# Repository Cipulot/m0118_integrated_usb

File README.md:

# m0118_integrated_usb

Drop-in replacement USB-C PCB for the Apple M0118 powered by QMK and VIAL.

## Daughterboard
The board comes with a snappable daughterboard with onboard USB-C. To avoid extra costs no connector is used. Instead the user will solder wires accordingly to the pin correspondence (marked on the PCB).

## Internal Wire
Internal wiring of a USB cable is possible. For this reason 2 holes on the pcb are available to the user. You can use them to tie down the cable using a zip tie for added stability.

An extra pin is provided, the `Shiled` pin. This is electrically connected to the board GND and it's solely used to avoid clipping the shielding wire off from the cable (if present at all).

### hahahahaha funny QR

## Firmware

~~Firmware is in development. Keep an eye out on the commits for it.~~

Firmware is OUT!! Precompiled VIAL `.hex` file downloadable [here](https://github.com/Cipulot/m0118_integrated_usb/blob/main/Firmware/HEX/m0118_integrated_usb_vial.hex).

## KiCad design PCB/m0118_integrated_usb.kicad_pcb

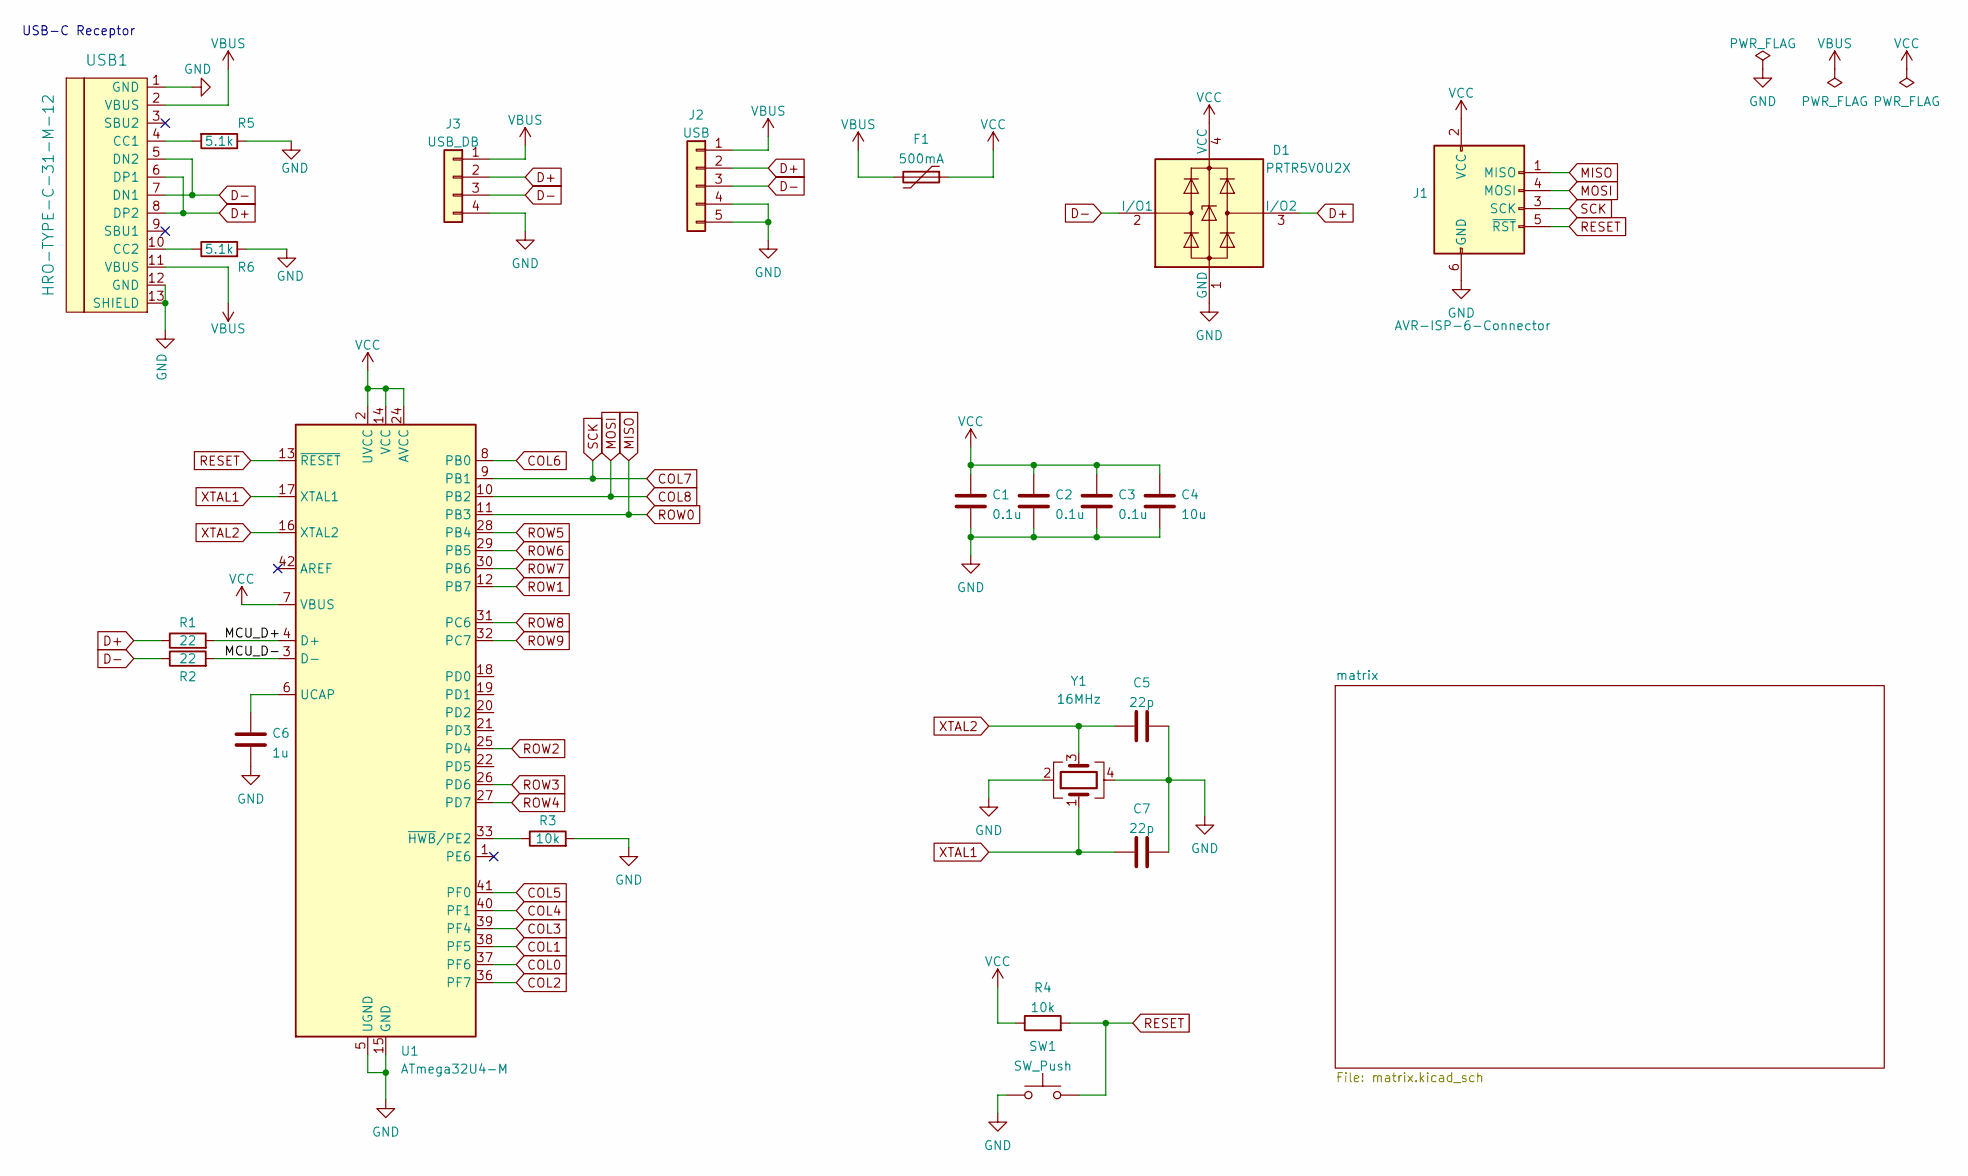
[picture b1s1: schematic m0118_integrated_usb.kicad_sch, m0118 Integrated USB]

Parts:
C1, C2, C3: 0.1u; C_0805_2012Metric
C4: 10u; C_0805_2012Metric
C5, C7: 22p; C_0805_2012Metric
C6: 1u; C_0805_2012Metric
D1: PRTR5V0U2X; SOT-143
F1: 500mA; Fuse_1206_3216Metric
J1: AVR-ISP-6-Connector; Reset_Pretty
J2: USB; PinHeader_1x05_P2.54mm_Vertical
J3: USB_DB; PinHeader_1x04_P2.54mm_Vertical
R1, R2: 22; R_0805_2012Metric
R3, R4: 10k; R_0805_2012Metric
R5, R6: 5.1k; R_0603_1608Metric
SW1: SW_Push; PinHeader_1x02_P2.54mm_Vertical
U1: ATmega32U4-M; QFN-44-1EP_7x7mm_P0.5mm_EP5.2x5.2mm
USB1: HRO-TYPE-C-31-M-12; HRO-TYPE-C-31-M-12-Assembly
Y1: 16MHz; Crystal_SMD_3225-4pin_3.2x2.5mm

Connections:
/MCU_D+: R1.2, U1.4 (D+)
/MCU_D-: R2.2, U1.3 (D-)
COL0: U1.37 (PF6); also elsewhere on the board
COL1: U1.38 (PF5); also elsewhere on the board
COL2: U1.36 (PF7); also elsewhere on the board
COL3: U1.39 (PF4); also elsewhere on the board
COL4: U1.40 (PF1); also elsewhere on the board
COL5: U1.41 (PF0); also elsewhere on the board
COL6: U1.8 (PB0); also elsewhere on the board
COL7: J1.3 (SCK), U1.9 (PB1); also elsewhere on the board
COL8: J1.4 (MOSI), U1.10 (PB2); also elsewhere on the board
D+: D1.3 (I/O2), J2.2, J3.2, R1.1, USB1.6 (DP1), USB1.8 (DP2)
D-: D1.2 (I/O1), J2.3, J3.3, R2.1, USB1.5 (DN2), USB1.7 (DN1)
GND: C1.2, C2.2, C3.2, C4.2, C5.1, C6.2, C7.1, D1.1 (GND), J1.6 (GND), J2.4, J2.5, J3.4, R3.2, R5.1, R6.2, SW1.1, U1.5 (UGND), U1.15 (GND), U1.23 (GND), U1.35 (GND), U1.43 (GND), U1.45 (GND), USB1.1 (GND), USB1.12 (GND), USB1.13 (SHIELD), Y1.2, Y1.4
MISO: J1.1 (MISO), U1.11 (PB3); also elsewhere on the board
unnamed: C6.1, U1.6 (UCAP)
unnamed: R3.1, U1.33 (~HWB/PE2)
unnamed: R5.2, USB1.4 (CC1)
unnamed: R6.1, USB1.10 (CC2)
RESET: J1.5 (~RST), R4.2, SW1.2, U1.13 (~RESET)
ROW1: U1.12 (PB7); also elsewhere on the board
ROW2: U1.25 (PD4); also elsewhere on the board
ROW3: U1.26 (PD6); also elsewhere on the board
ROW4: U1.27 (PD7); also elsewhere on the board
ROW5: U1.28 (PB4); also elsewhere on the board
ROW6: U1.29 (PB5); also elsewhere on the board
ROW7: U1.30 (PB6); also elsewhere on the board
ROW8: U1.31 (PC6); also elsewhere on the board
ROW9: U1.32 (PC7); also elsewhere on the board
VBUS: F1.2, J2.1, J3.1, USB1.2 (VBUS), USB1.11 (VBUS)
VCC: C1.1, C2.1, C3.1, C4.1, D1.4 (VCC), F1.1, J1.2 (VCC), R4.1, U1.2 (UVCC), U1.7 (VBUS), U1.14 (VCC), U1.24 (AVCC), U1.34 (VCC), U1.44 (AVCC)
XTAL1: C7.2, U1.17 (XTAL1), Y1.1
XTAL2: C5.2, U1.16 (XTAL2), Y1.3

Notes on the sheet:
USB-C Receptor

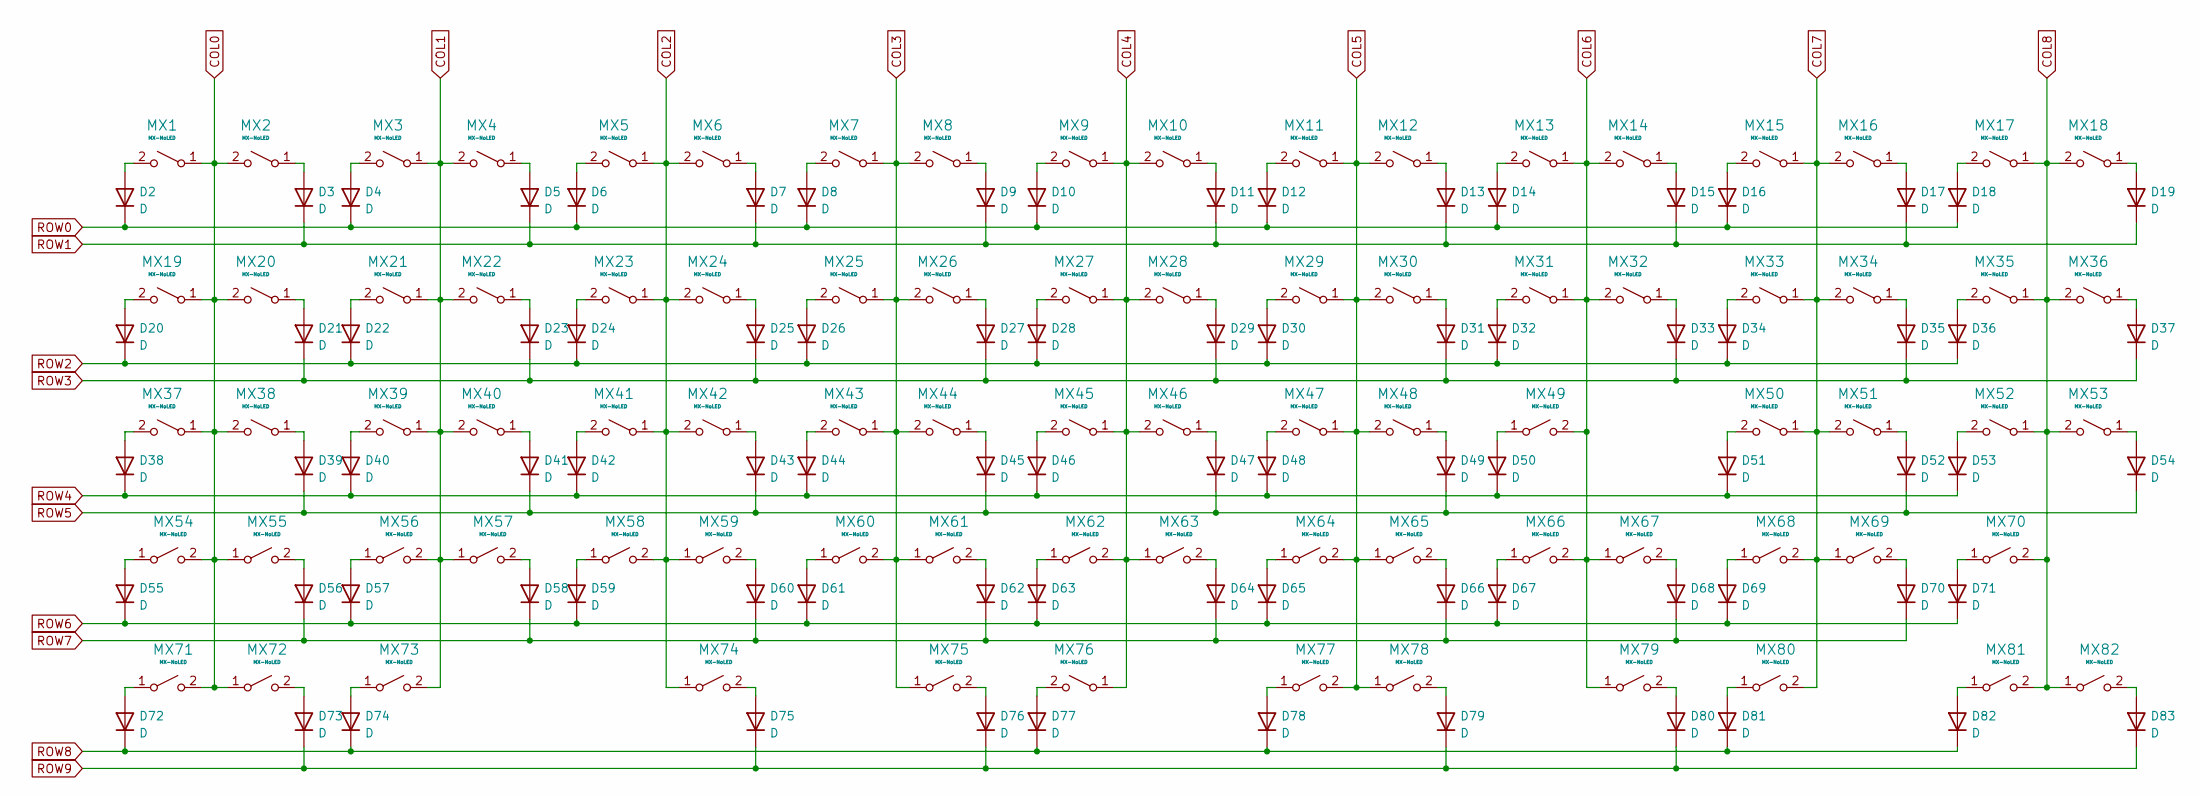
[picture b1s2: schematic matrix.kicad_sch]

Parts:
D2, D3, D4, D5, D6, D7, D8, D9, D10, D11, D12, D13, D14, D15, D16, D17, D18, D19, D20, D21, D22, D23, D24, D25, D26, D27, D28, D29, D30, D31, D32, D33, D34, D35, D36, D37, D38, D39, D40, D41, D42, D43, D44, D45, D46, D47, D48, D49, D50, D51, D52, D53, D54, D55, D56, D57, D58, D59, D60, D61, D62, D63, D64, D65, D66, D67, D68, D69, D70, D71, D72, D73, D74, D75, D76, D77, D78, D79, D80, D81, D82, D83: D; D_SOD-123
MX1, MX2, MX3, MX4, MX5, MX6, MX7, MX8, MX9, MX10, MX11, MX12, MX13, MX15, MX16, MX17, MX18, MX20, MX21, MX22, MX23, MX24, MX25, MX26, MX27, MX28, MX29, MX30, MX31, MX33, MX34, MX35, MX36, MX38, MX39, MX40, MX41, MX42, MX43, MX44, MX45, MX46, MX47, MX48, MX49, MX50, MX51, MX52, MX53, MX55, MX56, MX57, MX58, MX59, MX60, MX61, MX62, MX63, MX64, MX65, MX67, MX68, MX69, MX70, MX74, MX77, MX78, MX79, MX81: MX-NoLED; ALPS-1U
MX14, MX19, MX72: MX-NoLED; ALPS-1.5U
MX32: MX-NoLED; ALPS-SMALL-ISO
MX37, MX73, MX76: MX-NoLED; ALPS-1.75U
MX54, MX66, MX71: MX-NoLED; ALPS-1.25U
MX75: MX-NoLED; ALPS-5.25U
MX80, MX82: MX-NoLED; ALPS-2U

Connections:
COL0: MX1.1 (A), MX2.2 (B), MX19.1 (A), MX20.2 (B), MX37.1 (A), MX38.2 (B), MX54.2 (B), MX55.1 (A), MX71.2 (B), MX72.1 (A); also elsewhere on the board
COL1: MX3.1 (A), MX4.2 (B), MX21.1 (A), MX22.2 (B), MX39.1 (A), MX40.2 (B), MX56.2 (B), MX57.1 (A), MX73.2 (B); also elsewhere on the board
COL2: MX5.1 (A), MX6.2 (B), MX23.1 (A), MX24.2 (B), MX41.1 (A), MX42.2 (B), MX58.2 (B), MX59.1 (A), MX74.1 (A); also elsewhere on the board
COL3: MX7.1 (A), MX8.2 (B), MX25.1 (A), MX26.2 (B), MX43.1 (A), MX44.2 (B), MX60.2 (B), MX61.1 (A), MX75.1 (A); also elsewhere on the board
COL4: MX9.1 (A), MX10.2 (B), MX27.1 (A), MX28.2 (B), MX45.1 (A), MX46.2 (B), MX62.2 (B), MX63.1 (A), MX76.1 (A); also elsewhere on the board
COL5: MX11.1 (A), MX12.2 (B), MX29.1 (A), MX30.2 (B), MX47.1 (A), MX48.2 (B), MX64.2 (B), MX65.1 (A), MX77.2 (B), MX78.1 (A); also elsewhere on the board
COL6: MX13.1 (A), MX14.2 (B), MX31.1 (A), MX32.2 (B), MX49.2 (B), MX66.2 (B), MX67.1 (A), MX79.1 (A); also elsewhere on the board
COL7: MX15.1 (A), MX16.2 (B), MX33.1 (A), MX34.2 (B), MX50.1 (A), MX51.2 (B), MX68.2 (B), MX69.1 (A), MX80.2 (B); also elsewhere on the board
COL8: MX17.1 (A), MX18.2 (B), MX35.1 (A), MX36.2 (B), MX52.1 (A), MX53.2 (B), MX70.2 (B), MX81.2 (B), MX82.1 (A); also elsewhere on the board
MISO: D2.1 (K), D4.1 (K), D6.1 (K), D8.1 (K), D10.1 (K), D12.1 (K), D14.1 (K), D16.1 (K), D18.1 (K); also elsewhere on the board
unnamed: D2.2 (A), MX1.2 (B)
unnamed: D3.2 (A), MX2.1 (A)
unnamed: D4.2 (A), MX3.2 (B)
unnamed: D5.2 (A), MX4.1 (A)
unnamed: D6.2 (A), MX5.2 (B)
unnamed: D7.2 (A), MX6.1 (A)
unnamed: D8.2 (A), MX7.2 (B)
unnamed: D9.2 (A), MX8.1 (A)
unnamed: D10.2 (A), MX9.2 (B)
unnamed: D11.2 (A), MX10.1 (A)
unnamed: D12.2 (A), MX11.2 (B)
unnamed: D13.2 (A), MX12.1 (A)
unnamed: D14.2 (A), MX13.2 (B)
unnamed: D15.2 (A), MX14.1 (A)
unnamed: D16.2 (A), MX15.2 (B)
unnamed: D17.2 (A), MX16.1 (A)
unnamed: D18.2 (A), MX17.2 (B)
unnamed: D19.2 (A), MX18.1 (A)
unnamed: D20.2 (A), MX19.2 (B)
unnamed: D21.2 (A), MX20.1 (A)
unnamed: D22.2 (A), MX21.2 (B)
unnamed: D23.2 (A), MX22.1 (A)
unnamed: D24.2 (A), MX23.2 (B)
unnamed: D25.2 (A), MX24.1 (A)
unnamed: D26.2 (A), MX25.2 (B)
unnamed: D27.2 (A), MX26.1 (A)
unnamed: D28.2 (A), MX27.2 (B)
unnamed: D29.2 (A), MX28.1 (A)
unnamed: D30.2 (A), MX29.2 (B)
unnamed: D31.2 (A), MX30.1 (A)
unnamed: D32.2 (A), MX31.2 (B)
unnamed: D33.2 (A), MX32.1 (A)
unnamed: D34.2 (A), MX33.2 (B)
unnamed: D35.2 (A), MX34.1 (A)
unnamed: D36.2 (A), MX35.2 (B)
unnamed: D37.2 (A), MX36.1 (A)
unnamed: D38.2 (A), MX37.2 (B)
unnamed: D39.2 (A), MX38.1 (A)
unnamed: D40.2 (A), MX39.2 (B)
unnamed: D41.2 (A), MX40.1 (A)
unnamed: D42.2 (A), MX41.2 (B)
unnamed: D43.2 (A), MX42.1 (A)
unnamed: D44.2 (A), MX43.2 (B)
unnamed: D45.2 (A), MX44.1 (A)
unnamed: D46.2 (A), MX45.2 (B)
unnamed: D47.2 (A), MX46.1 (A)
unnamed: D48.2 (A), MX47.2 (B)
unnamed: D49.2 (A), MX48.1 (A)
unnamed: D50.2 (A), MX49.1 (A)
unnamed: D51.2 (A), MX50.2 (B)
unnamed: D52.2 (A), MX51.1 (A)
unnamed: D53.2 (A), MX52.2 (B)
unnamed: D54.2 (A), MX53.1 (A)
unnamed: D55.2 (A), MX54.1 (A)
unnamed: D56.2 (A), MX55.2 (B)
unnamed: D57.2 (A), MX56.1 (A)
unnamed: D58.2 (A), MX57.2 (B)
unnamed: D59.2 (A), MX58.1 (A)
unnamed: D60.2 (A), MX59.2 (B)
unnamed: D61.2 (A), MX60.1 (A)
unnamed: D62.2 (A), MX61.2 (B)
unnamed: D63.2 (A), MX62.1 (A)
unnamed: D64.2 (A), MX63.2 (B)
unnamed: D65.2 (A), MX64.1 (A)
unnamed: D66.2 (A), MX65.2 (B)
unnamed: D67.2 (A), MX66.1 (A)
unnamed: D68.2 (A), MX67.2 (B)
unnamed: D69.2 (A), MX68.1 (A)
unnamed: D70.2 (A), MX69.2 (B)
unnamed: D71.2 (A), MX70.1 (A)
unnamed: D72.2 (A), MX71.1 (A)
unnamed: D73.2 (A), MX72.2 (B)
unnamed: D74.2 (A), MX73.1 (A)
unnamed: D75.2 (A), MX74.2 (B)
unnamed: D76.2 (A), MX75.2 (B)
unnamed: D77.2 (A), MX76.2 (B)
unnamed: D78.2 (A), MX77.1 (A)
unnamed: D79.2 (A), MX78.2 (B)
unnamed: D80.2 (A), MX79.2 (B)
unnamed: D81.2 (A), MX80.1 (A)
unnamed: D82.2 (A), MX81.1 (A)
unnamed: D83.2 (A), MX82.2 (B)
ROW1: D3.1 (K), D5.1 (K), D7.1 (K), D9.1 (K), D11.1 (K), D13.1 (K), D15.1 (K), D17.1 (K), D19.1 (K); also elsewhere on the board
ROW2: D20.1 (K), D22.1 (K), D24.1 (K), D26.1 (K), D28.1 (K), D30.1 (K), D32.1 (K), D34.1 (K), D36.1 (K); also elsewhere on the board
ROW3: D21.1 (K), D23.1 (K), D25.1 (K), D27.1 (K), D29.1 (K), D31.1 (K), D33.1 (K), D35.1 (K), D37.1 (K); also elsewhere on the board
ROW4: D38.1 (K), D40.1 (K), D42.1 (K), D44.1 (K), D46.1 (K), D48.1 (K), D50.1 (K), D51.1 (K), D53.1 (K); also elsewhere on the board
ROW5: D39.1 (K), D41.1 (K), D43.1 (K), D45.1 (K), D47.1 (K), D49.1 (K), D52.1 (K), D54.1 (K); also elsewhere on the board
ROW6: D55.1 (K), D57.1 (K), D59.1 (K), D61.1 (K), D63.1 (K), D65.1 (K), D67.1 (K), D69.1 (K), D71.1 (K); also elsewhere on the board
ROW7: D56.1 (K), D58.1 (K), D60.1 (K), D62.1 (K), D64.1 (K), D66.1 (K), D68.1 (K), D70.1 (K); also elsewhere on the board
ROW8: D72.1 (K), D74.1 (K), D77.1 (K), D78.1 (K), D81.1 (K), D82.1 (K); also elsewhere on the board
ROW9: D73.1 (K), D75.1 (K), D76.1 (K), D79.1 (K), D80.1 (K), D83.1 (K); also elsewhere on the board

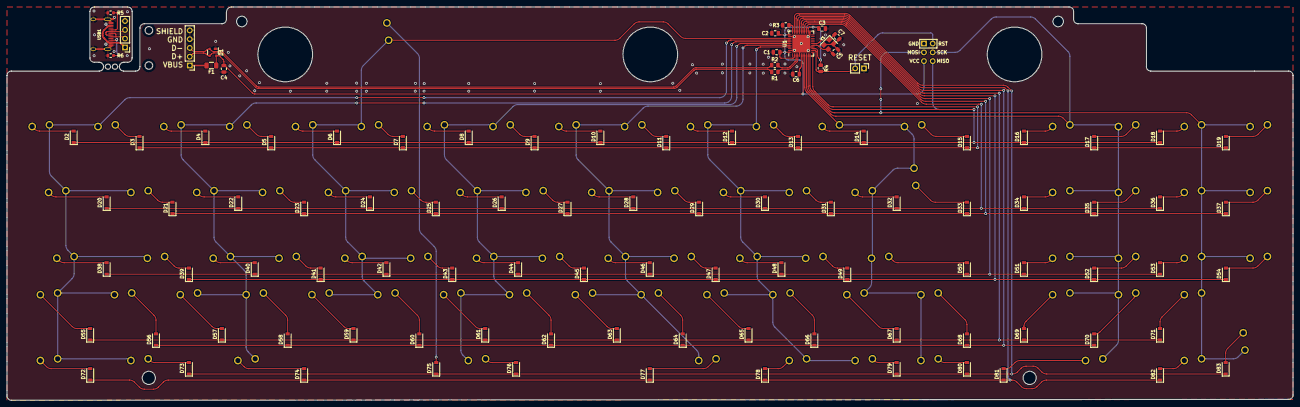
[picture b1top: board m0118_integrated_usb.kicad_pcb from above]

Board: 2 copper layers, 372.0 x 113.6 mm, 188 parts (0 on the bottom side), 115 nets.

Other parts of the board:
H22, H22#2: MountingHole; HOLE_M2

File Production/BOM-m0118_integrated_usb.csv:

Comment,Designator,Package,Quantity,LCSC
D,"D34,D60,D9,D57,D42,D65,D35,D21,D76,D10,D28,D56,D74,D58,D32,D61,D50,D17,D46,D48,D6,D52,D41,D38,D51,D7,D54,D19,D23,D63,D8,D69,D14,D33,D43,D78,D16,D55,D3,D22,D24,D44,D36,D82,D81,D15,D53,D75,D12,D68,D80,D49,D29,D67,D11,D77,D71,D79,D66,D70,D31,D25,D73,D62,D37,D13,D59,D18,D83,D26,D30,D5,D45,D72,D2,D47,D39,D4,D40,D27,D64,D20",D_SOD-123,82,C81598
22p,"C7,C5",C_0805_2012Metric,2,C1804
10k,"R4,R3",R_0805_2012Metric,2,C17414
22,"R2,R1",R_0805_2012Metric,2,C17561
5.1k,"R6,R5",R_0603_1608Metric,2,C27834
16MHz,Y1,Crystal_SMD_3225-4pin_3.2x2.5mm,1,C13738
500mA,F1,Fuse_1206_3216Metric,1,C70076
ATmega32U4-M,U1,QFN-44-1EP_7x7mm_P0.5mm_EP5.2x5.2mm,1,C45874
1u,C6,C_0805_2012Metric,1,C28323
PRTR5V0U2X,D1,SOT-143,1,C2827688
0.1u,"C1,C3,C2",C_0805_2012Metric,3,C49678
10u,C4,C_0805_2012Metric,1,C15850
HRO-TYPE-C-31-M-12,USB1,HRO-TYPE-C-31-M-12-Assembly,1,C165948

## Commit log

2022-04-28 Init
2022-04-28 Submodule Added
2022-04-28 Pics upload and README update
2022-04-28 Typo fix and KLE img add
2022-04-28 Updated to reflect use of Duplex
2022-04-29 Firmware Upload
    VIAL compatible firmware with precompiled HEX file.

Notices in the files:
PCB/m0118_integrated_usb.kicad_sch:
MIT License
